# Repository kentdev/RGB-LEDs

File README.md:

# RGB-LEDs
Controls for a strip of Radioshack tricolor LEDs

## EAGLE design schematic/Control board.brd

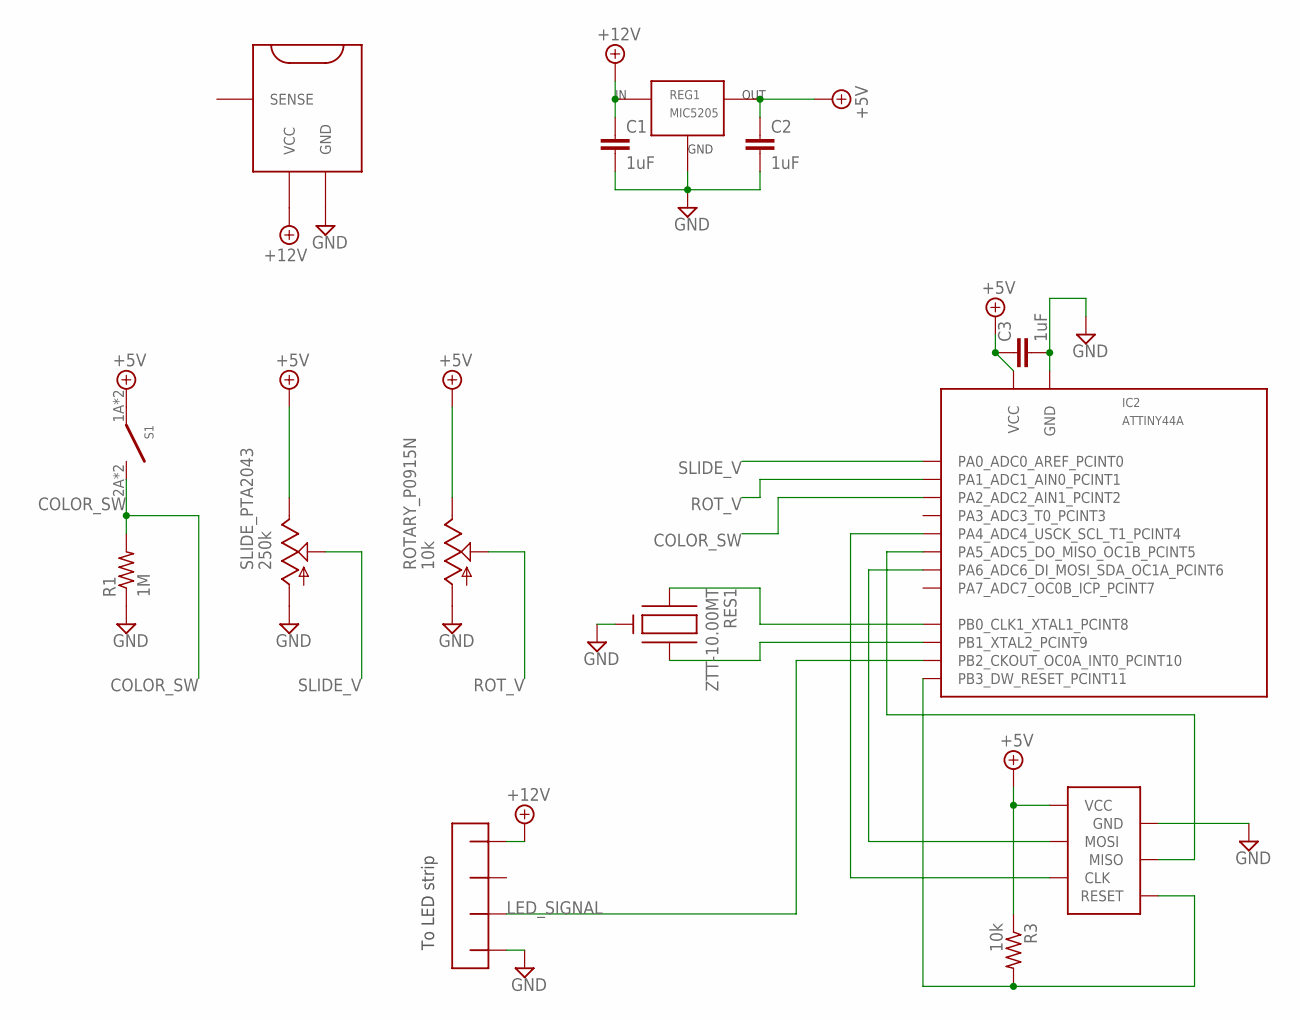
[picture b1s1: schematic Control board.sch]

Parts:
C1, C2, C3: 1uF; C0603
CONN1: 4-PIN-RIGHT-ANGLE; S5440
IC2: ATTINY44A; QFN-20
POW1: PJ-202A; PJ202A
R1: 1M; 0207/7
R3: 10k; 0207/7
REG1: MIC5205; SOT-23-5
RES1: ZTT-10.00MT; 3-PIN-THROUGH-HOLE
ROTARY_P0915N: 10k; P0915N
S1: D6R00
SLIDE_PTA2043: 250k; PTA2043
U$1: ISP

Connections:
+5V: C2.1, C3.1, IC2.P$9 (VCC), R3.1, REG1.5 (OUT), ROTARY_P0915N.R13 (B), S1.1A, S1.1B, SLIDE_PTA2043.P3 (B), U$1.VCC
+12V: C1.1, CONN1.P$4, POW1.1 (VCC), REG1.1 (IN), REG1.3 (IN)
COLOR_SW: IC2.P$3 (PA2_ADC2_AIN1_PCINT2), R1.2, S1.2A, S1.2B
GND: C1.2, C2.2, C3.2, CONN1.P$1, IC2.P$8 (GND), IC2.PAD (GND), POW1.2 (GND), R1.1, REG1.2 (GND), RES1.2 (GND), ROTARY_P0915N.R11 (A), SLIDE_PTA2043.P1 (A), U$1.GND
LED_SIGNAL: CONN1.P$2, IC2.P$14 (PB2_CKOUT_OC0A_INT0_PCINT10)
MISO: IC2.P$20 (PA5_ADC5_DO_MISO_OC1B_PCINT5), U$1.MISO
MOSI: IC2.P$16 (PA6_ADC6_DI_MOSI_SDA_OC1A_PCINT6), U$1.MOSI
unnamed: IC2.P$11 (PB0_CLK1_XTAL1_PCINT8), RES1.1 (X1)
unnamed: IC2.P$12 (PB1_XTAL2_PCINT9), RES1.3 (X2)
RESET: IC2.P$13 (PB3_DW_RESET_PCINT11), R3.2, U$1.RESET
ROT_V: IC2.P$4 (PA1_ADC1_AIN0_PCINT1), ROTARY_P0915N.R12 (S)
SCK: IC2.P$1 (PA4_ADC4_USCK_SCL_T1_PCINT4), U$1.SCK (CLK)
SLIDE_V: IC2.P$5 (PA0_ADC0_AREF_PCINT0), SLIDE_PTA2043.P2 (S)

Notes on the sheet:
To LED strip

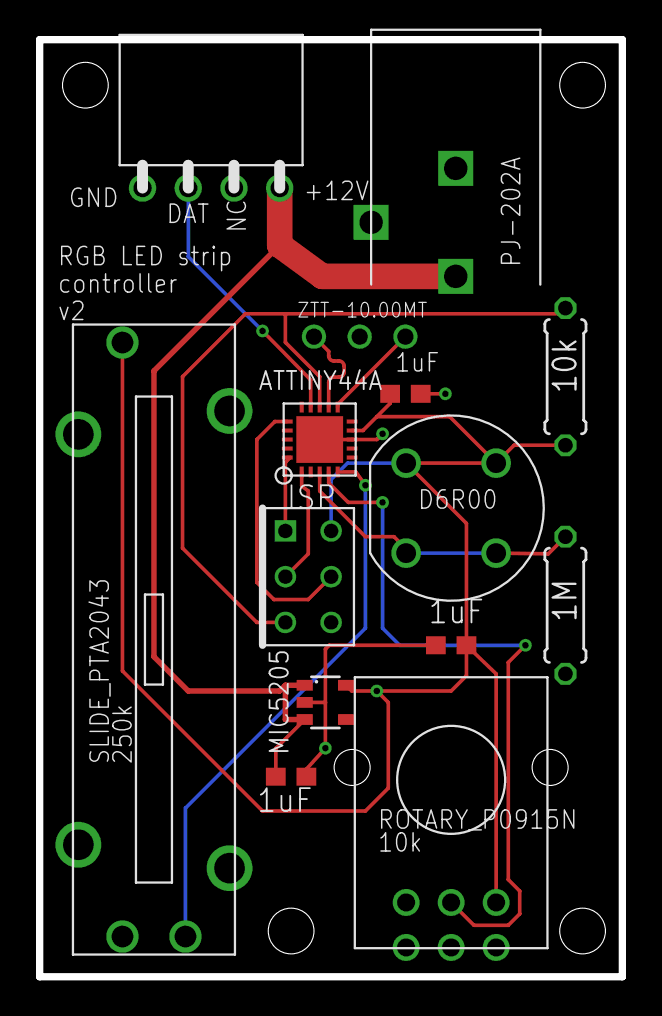
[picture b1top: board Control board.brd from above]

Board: 2 copper layers, 32.4 x 52.1 mm, 14 parts (0 on the bottom side), 13 nets.

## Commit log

2015-08-23 Added .gitignore
2015-08-23 Updated .gitignore and added modeling and schematic directories
2015-08-28 Added more library components and updated the board design
2015-08-29 Updated schematic, board file, and library; also updated the 3D model
2015-08-29 Voltage regulator and DIP microcontroller are too big, replacing with small SMD components
2015-08-30 Updated board with QFN-20 microcontroller
2015-08-30 Made the circuit board more compact
2015-08-30 Added a title to the board
2015-08-30 Fixed value layers and line widths
2015-09-01 Changed the resonator value from 16Mhz to 10MHz, for more accurate LED timing
2015-09-03 Began writing the code to read the controls and send commands to the LED strip
2015-09-06 Fixed LED port and improved sendToLED timings
2015-09-06 More progress accommodating the RGB LED strip timings, by squeezing the assembly code for every last cycle
2015-09-07 Finalized the sendToLED function, with timings accurate down to the clock cycle (0.1us)
2015-09-07 Removed debug code from sendToLED.c
2015-09-07 Added code to create a demo color wheel effect across the LEDs
2015-09-07 Fixed the bounding area of the potentiometer, and adjusted the value of the reset line's pull-up resistor
2015-09-07 Removed temporary file
2015-09-08 Added more comments describing the code
2015-09-13 Added #ifdef to switch between color demo and regular operation
2015-09-16 Barrel jack holes were way too big, fixed
2015-09-16 Fixed wrong outline of vertical rotary potentiometer
2015-09-17 Made the board a bit smaller, but there's still room to shrink it more
2015-09-18 Reduced the size of the control board
2015-09-18 Straightened a wire
2015-09-26 Added downloaded PJ-202A 3D model from Cui, Inc.
2015-09-26 Added the pin header to the board; board now has all relevant components attached
2015-10-18 Added controller code to adjust brightness, hue, and white/color mode
2015-10-23 Fixed comment
2015-10-23 Renamed the main file to main.c
2015-10-23 Updated makefile and removed unwanted -O2
2015-10-25 Added low-pass filtering to the slide potentiometer input
2015-11-10 Finished second draft of enclosure, now with face and separate top plate
2015-12-07 Working v1 enclosure
2015-12-07 Added code to balance the color coming the RGB LEDs, for a better white
2015-12-07 Added automatic shutdown if the LEDs have been left on without having their brightness changed for over 2 hours
2016-02-02 Reworked the main loop and made ADC use an interrupt
2016-02-11 Fixed port assignments, updated dead band code, reduced change deltas
2016-02-12 Added the beginnings of a low-power mode
2016-02-13 Scaled red back a little more, and reduced the timeout to 1 hour
2016-02-13 Fixed color demo artifacting
2016-02-14 Removed the color demo mode compilation switch, and instead made it activate if the color mode button is held for ~4 seconds before being released
